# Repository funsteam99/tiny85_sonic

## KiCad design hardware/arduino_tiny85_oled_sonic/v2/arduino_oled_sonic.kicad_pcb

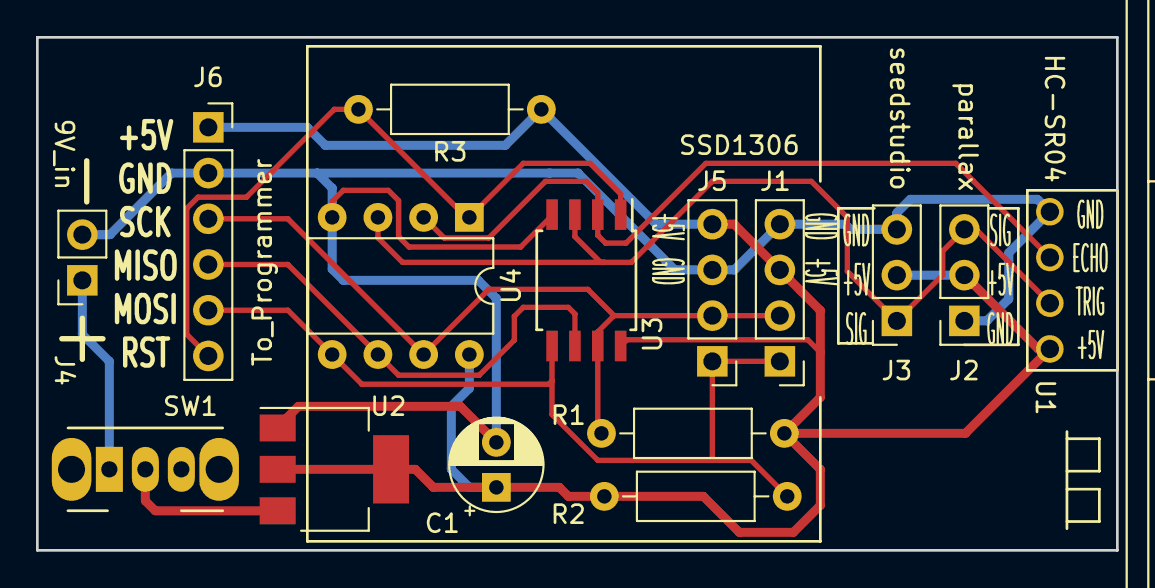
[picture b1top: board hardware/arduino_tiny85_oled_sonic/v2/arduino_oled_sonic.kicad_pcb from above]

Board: 2 copper layers, 60.0 x 28.5 mm, 15 parts (0 on the bottom side), 10 nets.

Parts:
C1: 10u; CP_Radial_D5.0mm_P2.50mm
J1, J5: SSD1306; PinHeader_1x04_P2.54mm_Vertical
J2: parallax; PinSocket_1x03_P2.54mm_Vertical
J3: seedstudio; PinSocket_1x03_P2.54mm_Vertical
J4: 9V_in; PinSocket_1x02_P2.54mm_Vertical
J6: To_Programmer; PinSocket_1x06_P2.54mm_Vertical
R1, R2, R3: 10k; R_Axial_DIN0207_L6.3mm_D2.5mm_P10.16mm_Horizontal
SW1: SW_SPST; SW_CuK_OS102011MA1QN1_SPDT_Angled
U1: HC-SR04; XCVR_HC-SR04
U2: LT1117-5.0; SOT-223-3_TabPin2
U3: ATtiny85-20SU; SOIJ-8_5.3x5.3mm_P1.27mm
U4: ATtiny85-20PU; DIP-8_W7.62mm

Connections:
+5V: C1.1, J1.3, J2.2, J3.2, J5.4, J6.1, R1.1, R2.1, R3.1, U1.1, U2.2, U3.8, U4.8
/Echo: U1.3, U3.2, U4.2
/MISO: J6.4, U3.6, U4.6
/RST: J6.6, R3.2, U3.1, U4.1
/SCL: J1.2, J5.2, J6.3, R1.2, U3.7, U4.7
/SDA: J1.1, J5.1, J6.5, R2.2, U3.5, U4.5
/Trig: J2.3, J3.1, U1.2, U3.3, U4.3
GND: C1.2, J1.4, J2.1, J3.3, J4.2, J5.3, J6.2, U1.4, U2.1, U3.4, U4.4
unnamed: J4.1, SW1.1
unnamed: SW1.2, U2.3

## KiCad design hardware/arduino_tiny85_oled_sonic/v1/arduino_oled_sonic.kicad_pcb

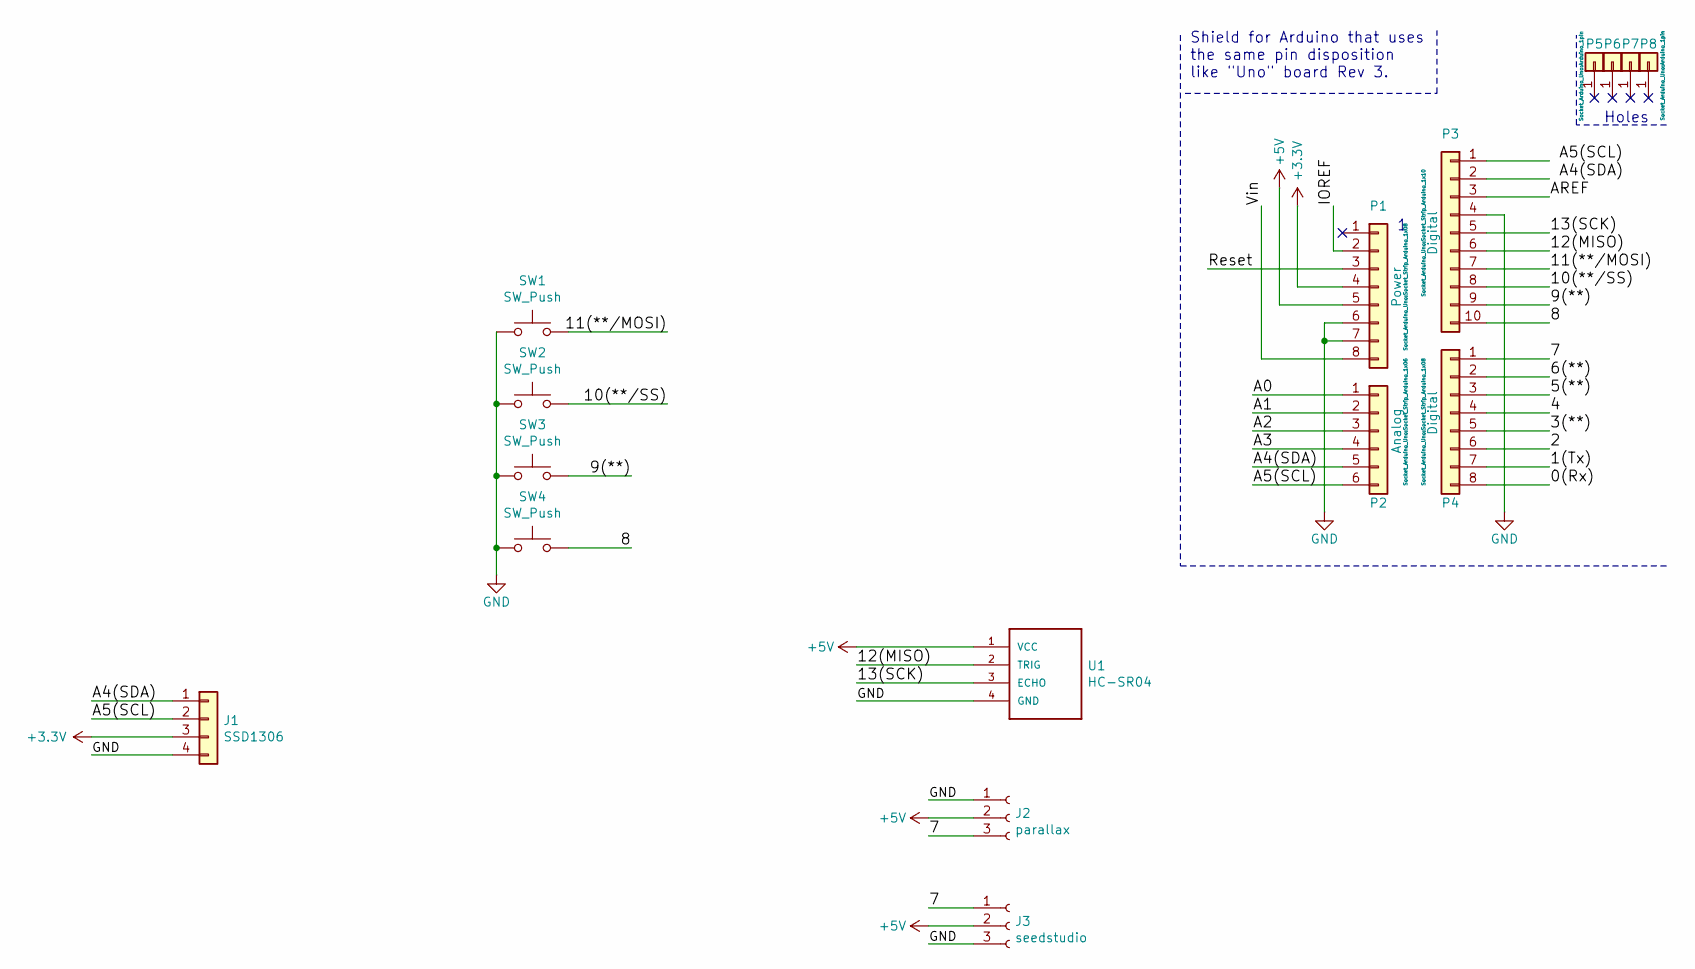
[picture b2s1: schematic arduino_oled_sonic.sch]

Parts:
J1: SSD1306; PinHeader_1x04_P2.54mm_Vertical
J2: parallax; PinSocket_1x03_P2.54mm_Vertical
J3: seedstudio; PinSocket_1x03_P2.54mm_Vertical
P1: Power; Socket_Strip_Arduino_1x08
P2: Analog; Socket_Strip_Arduino_1x06
P3: Digital; Socket_Strip_Arduino_1x10
P4: Digital; Socket_Strip_Arduino_1x08
P5, P6, P7, P8: CONN_01X01; Arduino_1pin
SW1, SW2, SW3, SW4: SW_Push; SW_PUSH_6mm_H5mm
U1: HC-SR04; XCVR_HC-SR04

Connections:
+3V3: J1.3, P1.4
+5V: J2.2, J3.2, P1.5, U1.1 (VCC)
/0(Rx): P4.8
/1(Tx): P4.7
/2: P4.6
/3(**): P4.5
/4: P4.4
/5(**): P4.3
/6(**): P4.2
/7: J2.3, J3.1, P4.1
/8: P3.10, SW4.2
/9(**): P3.9, SW3.2
/10(**/SS): P3.8, SW2.2
/11(**/MOSI): P3.7, SW1.2
/12(MISO): P3.6, U1.2 (TRIG)
/13(SCK): P3.5, U1.3 (ECHO)
/A0: P2.1
/A1: P2.2
/A2: P2.3
/A3: P2.4
/A4(SDA): J1.1, P2.5
/A5(SCL): J1.2, P2.6
/AREF: P3.3
/IOREF: P1.2
/Reset: P1.3
/Vin: P1.8
GND: J1.4, J2.1, J3.3, P1.6, P1.7, P3.4, SW1.1, SW2.1, SW3.1, SW4.1, U1.4 (GND)

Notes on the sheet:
Holes
Shield for Arduino that uses the same pin disposition like "Uno" board Rev 3.

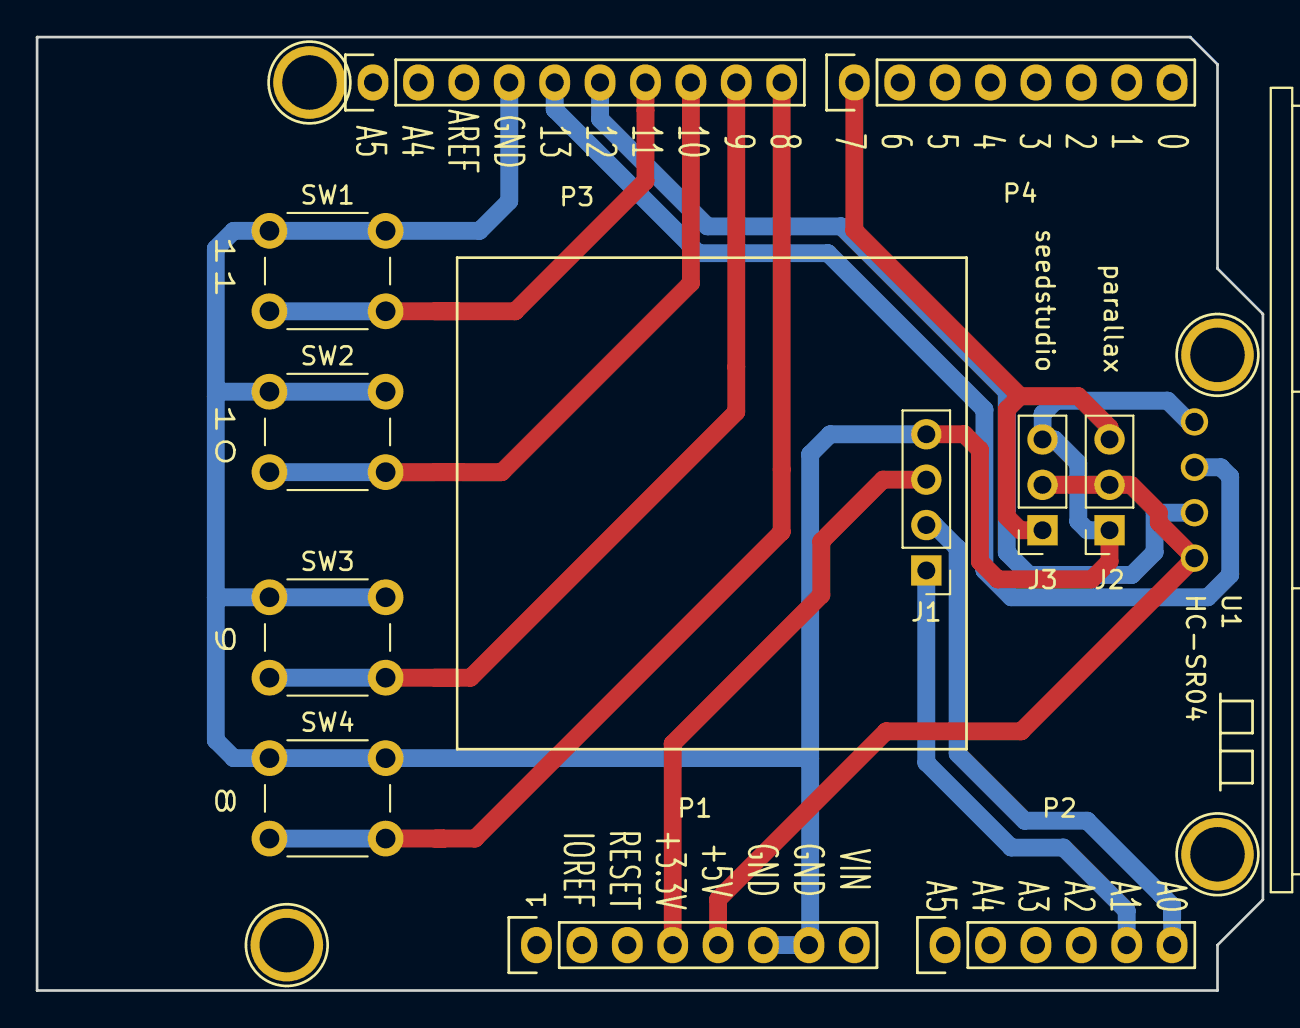
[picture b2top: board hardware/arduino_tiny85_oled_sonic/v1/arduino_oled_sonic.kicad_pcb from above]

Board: 2 copper layers, 68.6 x 53.3 mm, 16 parts (0 on the bottom side), 12 nets.
